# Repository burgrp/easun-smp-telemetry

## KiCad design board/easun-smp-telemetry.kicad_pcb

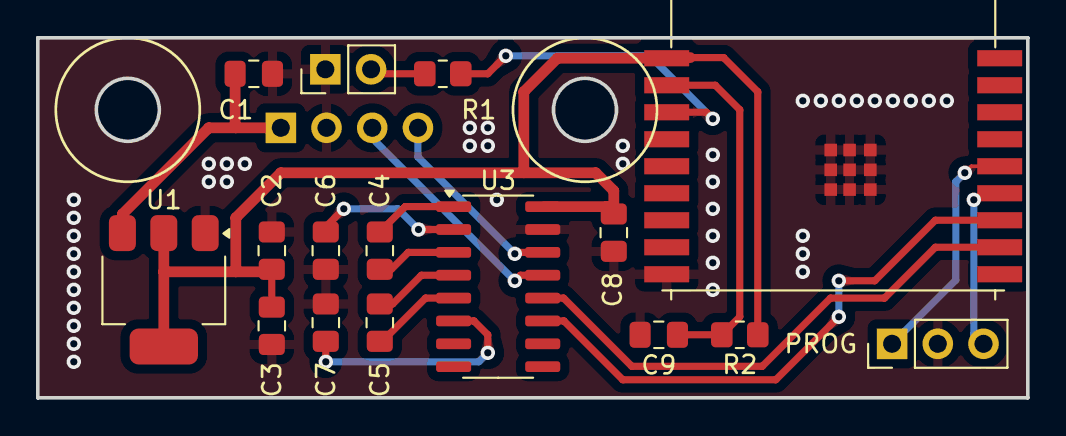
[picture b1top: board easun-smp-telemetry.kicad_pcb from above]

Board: 2 copper layers, 55.0 x 20.0 mm, 17 parts (1 on the bottom side), 17 nets.

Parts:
C1: 10u; C_0805_2012Metric_Pad1.18x1.45mm_HandSolder
C2, C3: 47u; C_0805_2012Metric_Pad1.18x1.45mm_HandSolder
C4, C5, C6, C7, C8: 100n; C_0805_2012Metric_Pad1.18x1.45mm_HandSolder
C9: 1u; C_0805_2012Metric_Pad1.18x1.45mm_HandSolder
D1: LED; PinHeader_1x02_P2.54mm_Vertical
J1: INVERTER; PinHeader_1x04_P2.54mm_Vertical
J2: PROG; PinHeader_1x03_P2.54mm_Vertical
R1: 270R; R_0805_2012Metric_Pad1.20x1.40mm_HandSolder
R2: 10k; R_0805_2012Metric_Pad1.20x1.40mm_HandSolder
U1: LM1117-3.3; SOT-223-3_TabPin2
U2: ESP32-C3-WROOM-02; ESP32-C3-WROOM-02 Handsolder
U3: MAX3232 (SP3232E); SOIC-16_3.9x9.9mm_P1.27mm

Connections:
+3V3: C2.1, C3.1, C8.1, R2.1, U1.2 (VO), U2.1 (3V3), U3.16 (VCC)
/RX_ESP: U2.11 (GPIO20/U0RXD), U3.12 (R1OUT)
/RX_INV: J1.4, U3.14 (T1OUT)
/TX_ESP: U2.12 (GPIO21/U0TXD), U3.11 (T1IN)
/TX_INV: J1.3, U3.13 (R1IN)
/USB_D+: J2.1, U2.14 (GPIO19/USB_D+)
/USB_D-: J2.3, U2.13 (GPIO18/USB_D-)
/VIN: C1.1, J1.1, U1.3 (VI)
GND: C1.2, C2.2, C3.2, C6.2, C7.2, C8.2, C9.2, D1.1 (K), J1.2, J2.2, U1.1 (GND), U2.9 (GND), U2.19 (GND), U3.15 (GND)
unnamed: D1.2 (A), R1.2
unnamed: C9.1, R2.2, U2.2 (EN/CHIP_PU)
unnamed: C4.1, U3.1 (C1+)
unnamed: C4.2, U3.3 (C1-)
unnamed: C5.1, U3.4 (C2+)
unnamed: C5.2, U3.5 (C2-)
unnamed: C6.1, U3.2 (VS+)
unnamed: C7.1, U3.6 (VS-)

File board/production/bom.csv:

Designator,Footprint,Quantity,Value,LCSC Part #
C1,0805,1,10u,
C2,0805,1,47u,
C3,0805,1,47u,
C4,0805,1,100n,
C5,0805,1,100n,
C6,0805,1,100n,
C7,0805,1,100n,
C8,0805,1,100n,
C9,0805,1,1u,
D1,PinHeader_1x02_P2.54mm_Vertical,1,LED,
J1,PinHeader_1x04_P2.54mm_Vertical,1,INVERTER,
J2,PinHeader_1x03_P2.54mm_Vertical,1,PROG,
R1,0805,1,270R,
R2,0805,1,10k,
U1,SOT-223-3_TabPin2,1,LM1117-3.3,
U2,ESP32-C3-WROOM-02 Handsolder,1,ESP32-C3-WROOM-02,
U3,SOIC-16_3.9x9.9mm_P1.27mm,1,MAX3232 (SP3232E),

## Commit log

2022-11-21 Coordinator CP
2023-02-17 Connection fix
2023-02-17 Fix of fix
2024-10-26 library update
